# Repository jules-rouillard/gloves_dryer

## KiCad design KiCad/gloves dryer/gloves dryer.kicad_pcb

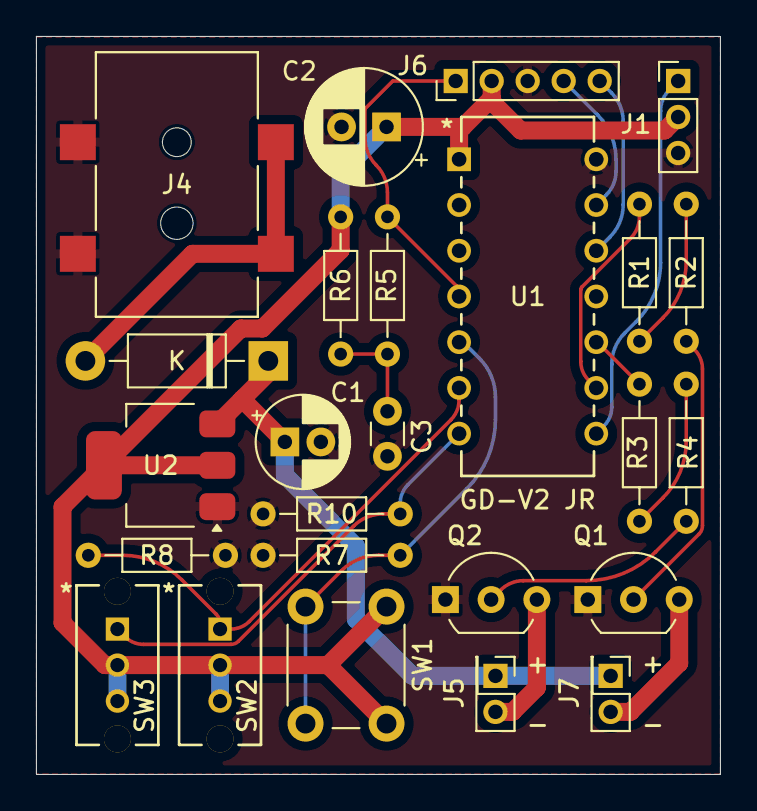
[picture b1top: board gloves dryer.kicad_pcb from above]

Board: 2 copper layers, 38.0 x 41.0 mm, 25 parts (0 on the bottom side), 20 nets.

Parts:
C1: 10u; CP_Radial_D5.0mm_P2.00mm
C2: 100u; CP_Radial_D6.3mm_P2.50mm
C3: 10p; C_Disc_D3.0mm_W1.6mm_P2.50mm
D1: 1N4007; D_DO-41_SOD81_P10.16mm_Horizontal
J1: Conn_01x03; PinHeader_1x03_P2.00mm_Vertical
J4: PJ-114AH-SMT-TR; SAMESKY_PJ-114AH-SMT-TR
J5, J7: Conn_01x02; PinHeader_2x01_P2.00mm_Vertical
J6: Conn_01x05; PinHeader_1x05_P2.00mm_Vertical
Q1, Q2: PN2222A; TO-92_Inline_Wide
R1, R3: 1k; R_Axial_DIN0204_L3.6mm_D1.6mm_P7.62mm_Horizontal
R2, R4: 5k; R_Axial_DIN0204_L3.6mm_D1.6mm_P7.62mm_Horizontal
R5: 220; R_Axial_DIN0204_L3.6mm_D1.6mm_P7.62mm_Horizontal
R6, R7, R8, R10: 10k; R_Axial_DIN0204_L3.6mm_D1.6mm_P7.62mm_Horizontal
SW1: SW_Push_Dual; SW_PUSH_6mm_H5mm
SW2, SW3: OS102011MS2QN1; SPDT_OS102011_CNK
U1: PIC16F18126-I/P; PDIP14_P_MCH
U2: AMS1117-5.0; SOT-223-3_TabPin2

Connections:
/BT1: R7.2, SW1.2, U1.5 (RC5)
/CLK: J6.5, U1.12 (RA1/ICSPCLK)
/DAT: J6.4, U1.13 (RA0/ICSPDAT)
/F1-: J5.2, Q2.3 (C)
/F2-: J7.2, Q1.3 (C)
/IF1: R3.1, U1.10 (RC0)
/IF2: R1.1, U1.9 (RC1)
/IO_SENS: J1.1, U1.8 (RC2)
/MCLR: J6.1, R5.2, U1.4 (RA3/*MCLR/VPP)
/SW1: R8.2, SW2.1, U1.6 (RC4)
/SW2: R10.2, SW3.1, U1.7 (RC3)
/VDDG_12V: C1.1, D1.1 (K), J5.1, J7.1, U2.3 (VI)
/VDD_5V: C2.1, J1.2, J6.2, R6.2, SW1.1, SW2.2, SW2.3, SW3.2, SW3.3, U1.1 (VDD), U2.2 (VO)
/VDD_12V: D1.2 (A), J4.1_1, J4.1_2
GND: C1.2, C2.2, C3.2, J1.3, J4.2, J4.3, J6.3, Q1.1 (E), Q2.1 (E), R7.1, R8.1, R10.1, U1.14 (VSS), U2.1 (GND)
unnamed: C3.1, R5.1, R6.1
unnamed: Q1.2 (B), R2.2
unnamed: Q2.2 (B), R4.2
unnamed: R1.2, R2.1
unnamed: R3.2, R4.1

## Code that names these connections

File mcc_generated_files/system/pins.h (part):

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// get/set IO_RC0 aliases
#define IO_RC0_TRIS                 TRISCbits.TRISC0
#define IO_RC0_LAT                  LATCbits.LATC0
#define IO_RC0_PORT                 PORTCbits.RC0
#define IO_RC0_WPU                  WPUCbits.WPUC0
#define IO_RC0_OD                   ODCONCbits.ODCC0
#define IO_RC0_ANS                  ANSELCbits.ANSC0
#define IO_RC0_SetHigh()            do { LATCbits.LATC0 = 1; } while(0)
#define IO_RC0_SetLow()             do { LATCbits.LATC0 = 0; } while(0)
#define IO_RC0_Toggle()             do { LATCbits.LATC0 = ~LATCbits.LATC0; } while(0)
#define IO_RC0_GetValue()           PORTCbits.RC0
#define IO_RC0_SetDigitalInput()    do { TRISCbits.TRISC0 = 1; } while(0)
#define IO_RC0_SetDigitalOutput()   do { TRISCbits.TRISC0 = 0; } while(0)
#define IO_RC0_SetPullup()          do { WPUCbits.WPUC0 = 1; } while(0)
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// get/set IO_RC1 aliases
#define IO_RC1_TRIS                 TRISCbits.TRISC1
#define IO_RC1_LAT                  LATCbits.LATC1
#define IO_RC1_PORT                 PORTCbits.RC1
#define IO_RC1_WPU                  WPUCbits.WPUC1
#define IO_RC1_OD                   ODCONCbits.ODCC1
#define IO_RC1_ANS                  ANSELCbits.ANSC1
#define IO_RC1_SetHigh()            do { LATCbits.LATC1 = 1; } while(0)
#define IO_RC1_SetLow()             do { LATCbits.LATC1 = 0; } while(0)
#define IO_RC1_Toggle()             do { LATCbits.LATC1 = ~LATCbits.LATC1; } while(0)
#define IO_RC1_GetValue()           PORTCbits.RC1
#define IO_RC1_SetDigitalInput()    do { TRISCbits.TRISC1 = 1; } while(0)
#define IO_RC1_SetDigitalOutput()   do { TRISCbits.TRISC1 = 0; } while(0)
#define IO_RC1_SetPullup()          do { WPUCbits.WPUC1 = 1; } while(0)
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// get/set IO_RC2 aliases
#define IO_RC2_TRIS                 TRISCbits.TRISC2
#define IO_RC2_LAT                  LATCbits.LATC2
#define IO_RC2_PORT                 PORTCbits.RC2
#define IO_RC2_WPU                  WPUCbits.WPUC2
#define IO_RC2_OD                   ODCONCbits.ODCC2
#define IO_RC2_ANS                  ANSELCbits.ANSC2
#define IO_RC2_SetHigh()            do { LATCbits.LATC2 = 1; } while(0)
#define IO_RC2_SetLow()             do { LATCbits.LATC2 = 0; } while(0)
#define IO_RC2_Toggle()             do { LATCbits.LATC2 = ~LATCbits.LATC2; } while(0)
#define IO_RC2_GetValue()           PORTCbits.RC2
#define IO_RC2_SetDigitalInput()    do { TRISCbits.TRISC2 = 1; } while(0)
#define IO_RC2_SetDigitalOutput()   do { TRISCbits.TRISC2 = 0; } while(0)
#define IO_RC2_SetPullup()          do { WPUCbits.WPUC2 = 1; } while(0)
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// get/set IO_RC3 aliases
#define IO_RC3_TRIS                 TRISCbits.TRISC3
#define IO_RC3_LAT                  LATCbits.LATC3
#define IO_RC3_PORT                 PORTCbits.RC3
#define IO_RC3_WPU                  WPUCbits.WPUC3
#define IO_RC3_OD                   ODCONCbits.ODCC3
#define IO_RC3_ANS                  ANSELCbits.ANSC3
#define IO_RC3_SetHigh()            do { LATCbits.LATC3 = 1; } while(0)
#define IO_RC3_SetLow()             do { LATCbits.LATC3 = 0; } while(0)
#define IO_RC3_Toggle()             do { LATCbits.LATC3 = ~LATCbits.LATC3; } while(0)
#define IO_RC3_GetValue()           PORTCbits.RC3
#define IO_RC3_SetDigitalInput()    do { TRISCbits.TRISC3 = 1; } while(0)
#define IO_RC3_SetDigitalOutput()   do { TRISCbits.TRISC3 = 0; } while(0)
#define IO_RC3_SetPullup()          do { WPUCbits.WPUC3 = 1; } while(0)
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// get/set IO_RC4 aliases
#define IO_RC4_TRIS                 TRISCbits.TRISC4
#define IO_RC4_LAT                  LATCbits.LATC4
#define IO_RC4_PORT                 PORTCbits.RC4
#define IO_RC4_WPU                  WPUCbits.WPUC4
#define IO_RC4_OD                   ODCONCbits.ODCC4
#define IO_RC4_ANS                  ANSELCbits.ANSC4
#define IO_RC4_SetHigh()            do { LATCbits.LATC4 = 1; } while(0)
#define IO_RC4_SetLow()             do { LATCbits.LATC4 = 0; } while(0)
#define IO_RC4_Toggle()             do { LATCbits.LATC4 = ~LATCbits.LATC4; } while(0)
#define IO_RC4_GetValue()           PORTCbits.RC4
#define IO_RC4_SetDigitalInput()    do { TRISCbits.TRISC4 = 1; } while(0)
#define IO_RC4_SetDigitalOutput()   do { TRISCbits.TRISC4 = 0; } while(0)
#define IO_RC4_SetPullup()          do { WPUCbits.WPUC4 = 1; } while(0)
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// get/set IO_RC5 aliases
#define IO_RC5_TRIS                 TRISCbits.TRISC5
#define IO_RC5_LAT                  LATCbits.LATC5
#define IO_RC5_PORT                 PORTCbits.RC5
#define IO_RC5_WPU                  WPUCbits.WPUC5
#define IO_RC5_OD                   ODCONCbits.ODCC5
#define IO_RC5_ANS                  ANSELCbits.ANSC5
#define IO_RC5_SetHigh()            do { LATCbits.LATC5 = 1; } while(0)
#define IO_RC5_SetLow()             do { LATCbits.LATC5 = 0; } while(0)
#define IO_RC5_Toggle()             do { LATCbits.LATC5 = ~LATCbits.LATC5; } while(0)
#define IO_RC5_GetValue()           PORTCbits.RC5
#define IO_RC5_SetDigitalInput()    do { TRISCbits.TRISC5 = 1; } while(0)
#define IO_RC5_SetDigitalOutput()   do { TRISCbits.TRISC5 = 0; } while(0)
#define IO_RC5_SetPullup()          do { WPUCbits.WPUC5 = 1; } while(0)
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
/**
 * @ingroup  pinsdriver
 * @brief Interrupt on Change Handler for the IO_RC5 pin functionality
 * @param none
 * @return none
 */
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
/**
 * @ingroup  pinsdriver
 * @brief Interrupt Handler Setter for IO_RC5 pin interrupt-on-change functionality.
 *        Allows selecting an interrupt handler for IO_RC5 at application runtime.
 * @pre Pins intializer called
 * @param InterruptHandler function pointer.
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
/**
 * @ingroup  pinsdriver
 * @brief Dynamic Interrupt Handler for IO_RC5 pin.
 *        This is a dynamic interrupt handler to be used together with the IO_RC5_SetInterruptHandler() method.
 *        This handler is called every time the IO_RC5 ISR is executed and allows any function to be registered at runtime.
 * @pre Pins intializer called
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
/**
 * @ingroup  pinsdriver
 * @brief Default Interrupt Handler for IO_RC5 pin. 
 *        This is a predefined interrupt handler to be used together with the IO_RC5_SetInterruptHandler() method.
 *        This handler is called every time the IO_RC5 ISR is executed. 
 * @pre Pins intializer called
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
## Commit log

2025-03-12 Added porject file from MPLAB X IDE. Project was started and finished on the weekend of 18-19th May 2024. Some minor update to the behaviour are still planned.
2025-03-17 started work on kicad added symbole and foot print for pic16F18126,the goal is to generate pcb layout and have a digital version of the circuit no just on a paper
2025-03-19 Finish V2 schematic with added button and first PCB layout, tolarance have to be double check before sending for manufacturing
2025-03-22 Finished PCB, working on firmware for added switch state
2025-04-09 Updated firmware for version two of the project, as well as kicad file for version 2

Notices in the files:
mcc_generated_files/system/pins.h:
© [2025] Microchip Technology Inc. and its subsidiaries.
